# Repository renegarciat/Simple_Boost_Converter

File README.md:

# Simple_Boost_Converter
 PCB for a simple boost converter

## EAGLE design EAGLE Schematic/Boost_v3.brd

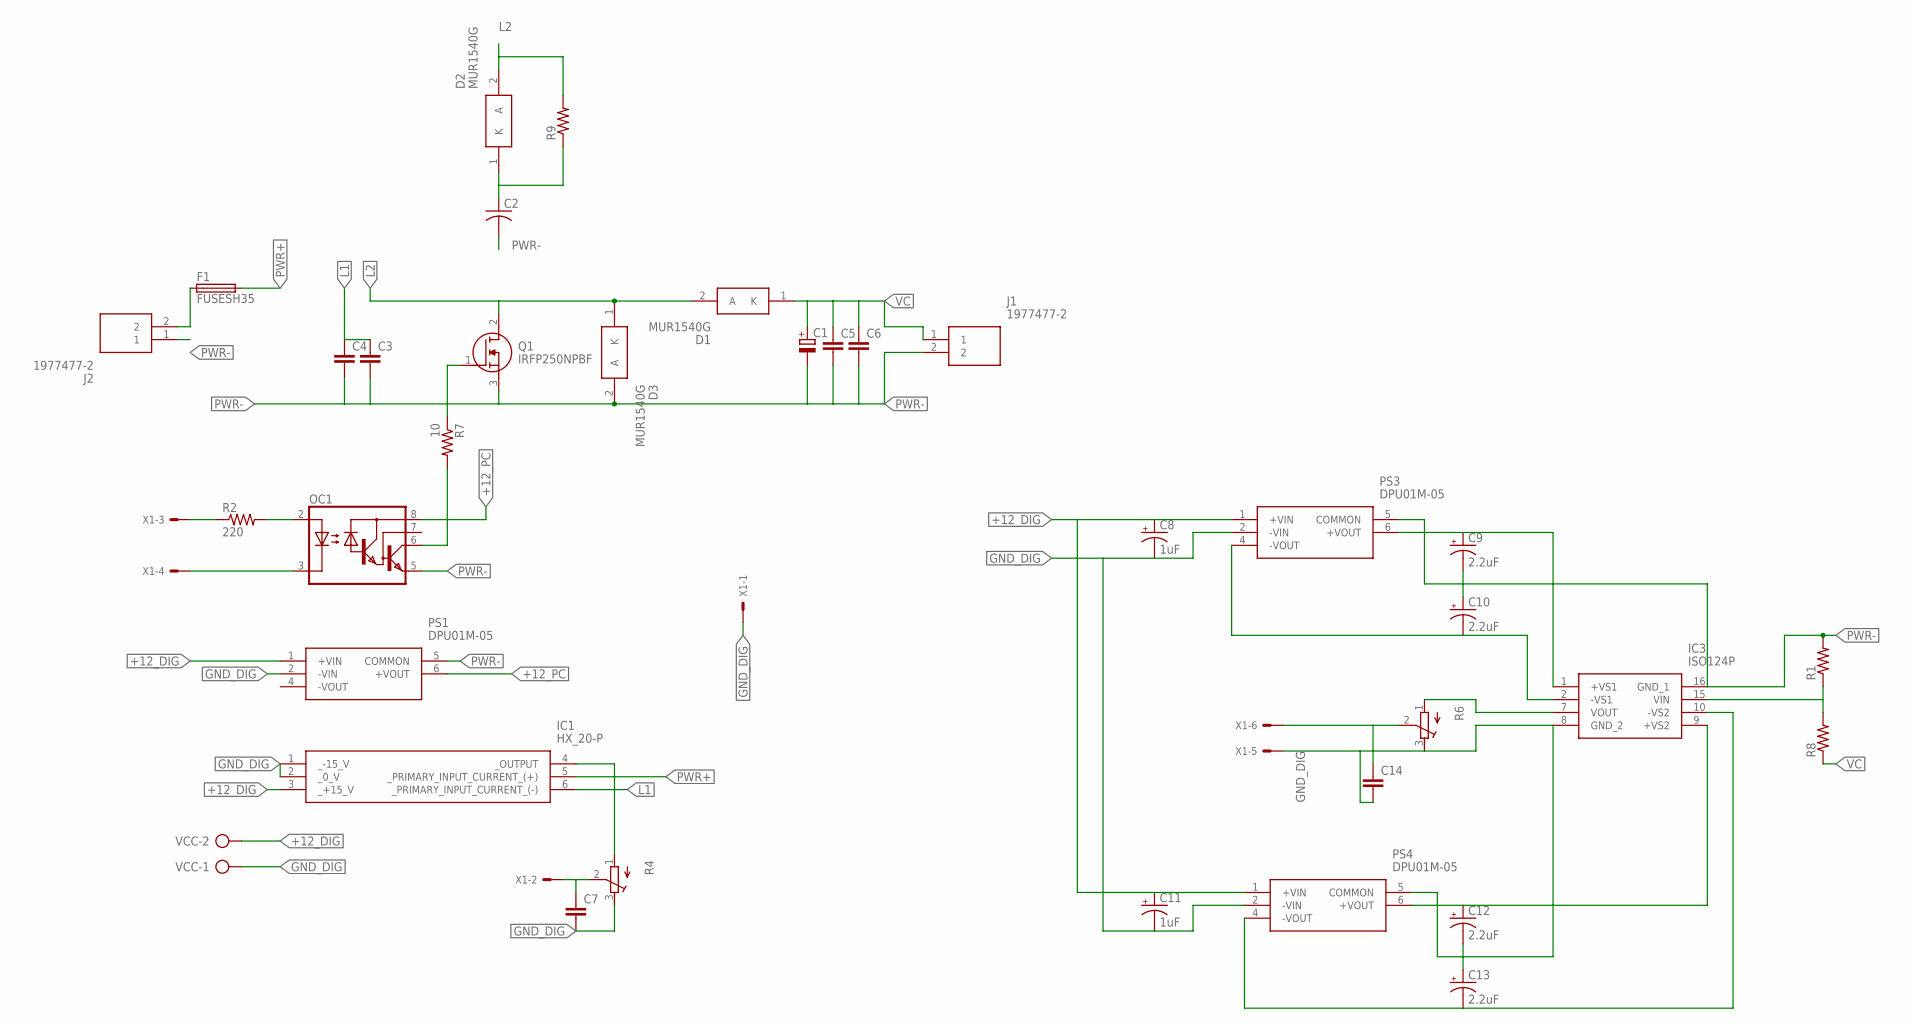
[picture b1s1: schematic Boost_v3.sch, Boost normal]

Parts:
C1: CPOL-EUE10-35; EB35D
C2: C-US050-025X075; C050-025X075
C3, C4, C5, C6, C7, C14: C-EU050-030X075; C050-030X075
C8, C11: 1uF; E2,5-5
C9, C10, C12, C13: 2.2uF; E2,5-5
D1, D2, D3: MUR1540G; TO533P482X997X1956-2P
F1: FUSESH35; SH25
IC1: HX_20-P; HX20P
IC3: ISO124P; DIP254P762X533-8P
J1, J2: 1977477-2; SHDR2W165P0X825_1X2_1650X1370X
OC1: 6N138; DIL08
PS1, PS3, PS4: DPU01M-05; DPU01M05
Q1: IRFP250NPBF; TO545P530X1560X2460-3P
R1, R8, R9: R-US_VTA52; VTA52
R2: 220; 0207/10
R4, R6: R-TRIMM64W; RTRIM64W
R7: 10; 0207/10
VCC: AK500/2
X1: 22-23-2061

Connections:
+12_DIG: C8.+, C11.+, IC1.3 (_+15_V), PS1.1 (+VIN), PS3.1 (+VIN), PS4.1 (+VIN), VCC.2
+12_PC: OC1.8 (VCC), PS1.6 (+VOUT)
GND_DIG: C7.2, C8.-, C11.-, C12.-, C13.+, C14.2, IC1.1 (_-15_V), IC1.2 (_0_V), IC3.8 (GND_2), PS1.2 (-VIN), PS3.2 (-VIN), PS4.2 (-VIN), PS4.5 (COMMON), R4.3 (E), R6.3 (E), VCC.1, X1.1, X1.5
L1: C3.1, C4.1, IC1.6 (_PRIMARY_INPUT_CURRENT_(-))
L2: D1.2 (A), D2.2 (A), D3.1 (K), Q1.2 (D), R9.2
unnamed: OC1.2 (A), R2.2
unnamed: Q1.1 (G), R7.1
unnamed: C7.1, R4.2 (S), X1.2
unnamed: C2.1, D2.1 (K), R9.1
unnamed: OC1.6 (VO), R7.2
unnamed: R2.1, X1.3
unnamed: OC1.3 (C), X1.4
unnamed: C14.1, R6.2 (S), X1.6
unnamed: IC1.4 (_OUTPUT), R4.1 (A)
unnamed: F1.1, J2.2
unnamed: C9.+, IC3.1 (+VS1), PS3.6 (+VOUT)
unnamed: C10.-, IC3.2 (-VS1), PS3.4 (-VOUT)
unnamed: C12.+, IC3.9 (+VS2), PS4.6 (+VOUT)
unnamed: C13.-, IC3.10 (-VS2), PS4.4 (-VOUT)
unnamed: IC3.15 (VIN), R1.1, R8.2
unnamed: IC3.7 (VOUT), R6.1 (A)
PWR+: F1.2, IC1.5 (_PRIMARY_INPUT_CURRENT_(+))
PWR-: C1.-, C2.2, C3.2, C4.2, C5.2, C6.2, C9.-, C10.+, D3.2 (A), IC3.16 (GND_1), J1.2, J2.1, OC1.5 (GND), PS1.5 (COMMON), PS3.5 (COMMON), Q1.3 (S), R1.2
VC: C1.+, C5.1, C6.1, D1.1 (K), J1.1, R8.1

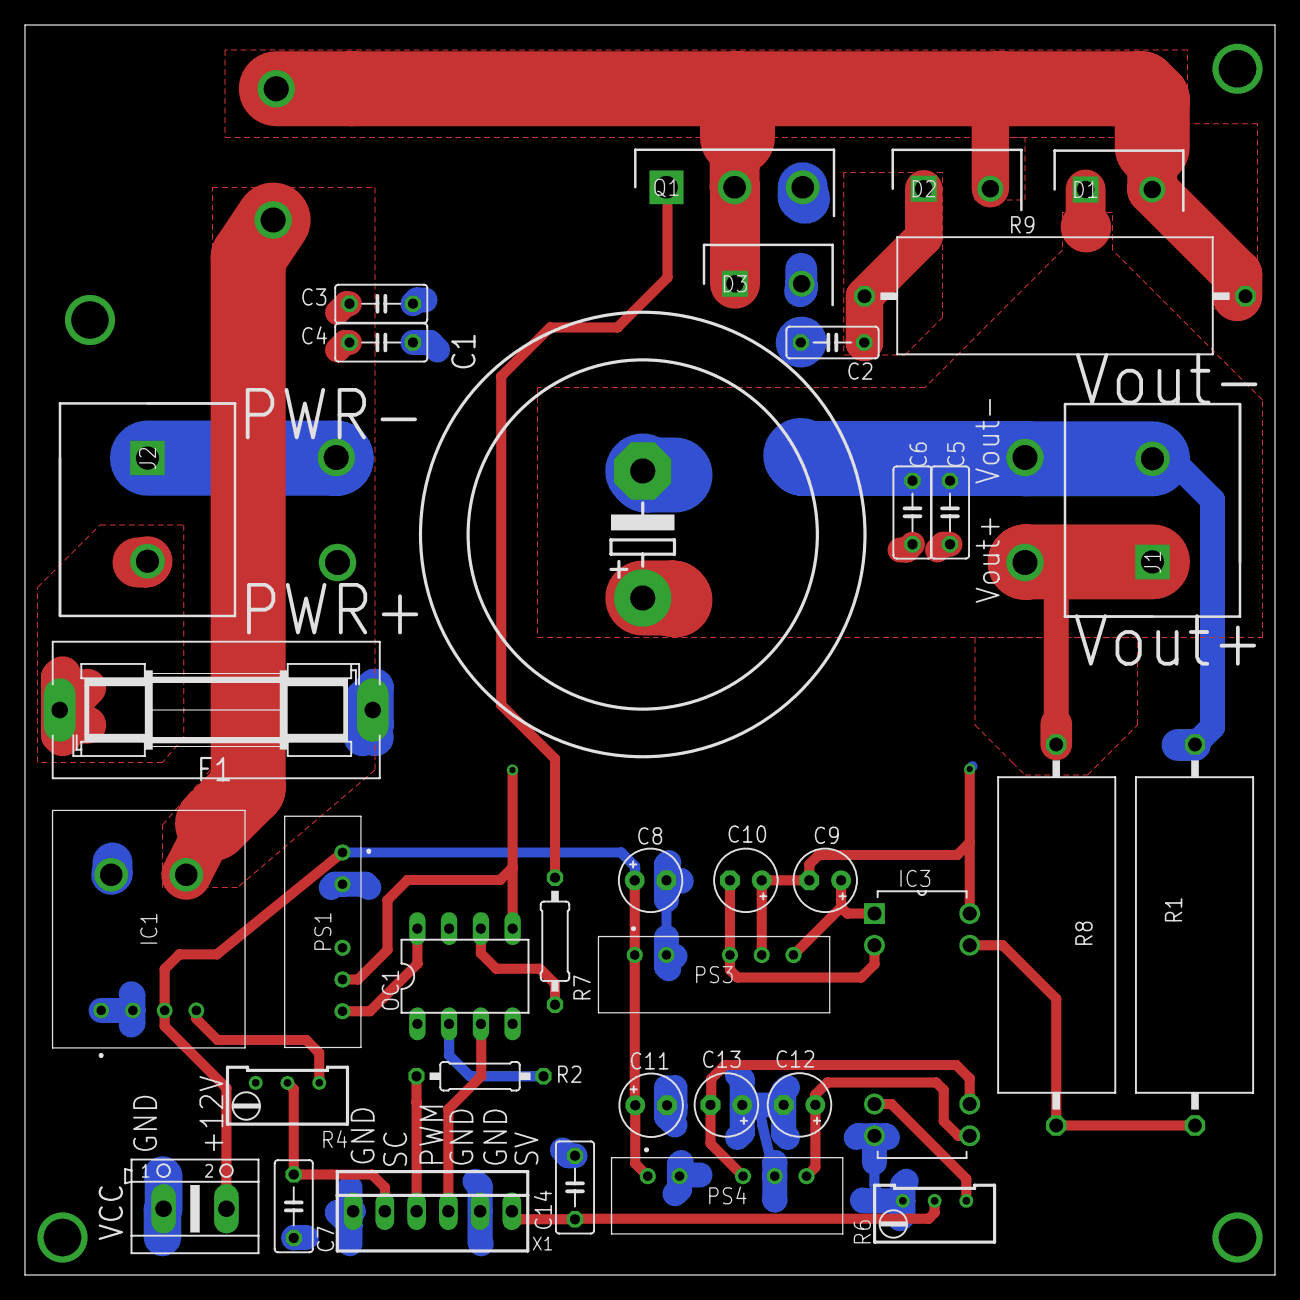
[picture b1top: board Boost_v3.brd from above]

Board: 2 copper layers, 100.0 x 100.0 mm, 36 parts (0 on the bottom side), 24 nets.

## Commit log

2023-03-06 New files
2023-03-06 Division of two separate software projects
2023-03-06 Updated libraries
    Updated libraries Of proteus
2023-03-07 Footprint change of Iso124P
2023-03-07 Population of PCB
2023-03-07 Updated names of nets (PWR Type)
2023-03-07 Some control pieces added
2023-03-08 First iteration
2023-03-16 Added some changes
2023-03-17 16/03
2023-05-03 Deleted Eagle Buck schematic
    Replaced by Altium design instead.
2023-05-03 revision
